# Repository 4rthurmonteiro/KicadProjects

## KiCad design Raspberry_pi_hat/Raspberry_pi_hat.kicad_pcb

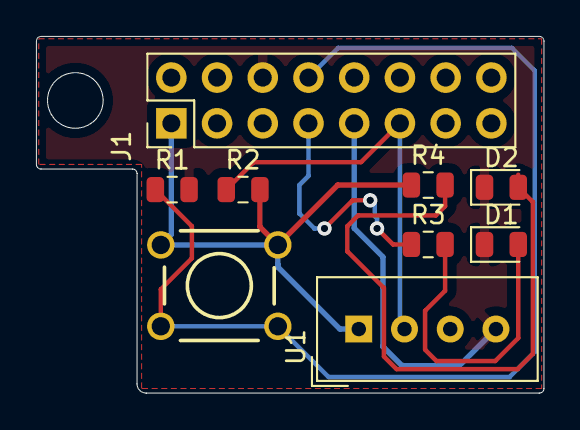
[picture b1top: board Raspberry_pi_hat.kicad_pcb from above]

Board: 2 copper layers, 28.2 x 19.8 mm, 9 parts (0 on the bottom side), 7 nets.

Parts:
D1, D2: LED; LED_0805_2012Metric
J1: Raspberry_Pi_2_3; PinHeader_2x08_P2.54mm_Vertical
R1, R2, R3, R4: R; R_0805_2012Metric
SW1: SW_DPST; SW_PUSHBUTTON_PTH
U1: DHT22; Aosong_DHT11_5.5x12.0_P2.54mm

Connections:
/3V3: J1.1, R2.2, R4.1, SW1.1, U1.1
/BUTTON_INPUT: J1.8, R1.1, SW1.2
/LED_OUTPUT: J1.7, R3.1
GND: D1.1, D2.1, J1.6, J1.9, R1.2, U1.4
unnamed: D1.2, R3.2
unnamed: D2.2, R4.2
unnamed: J1.11, R2.1, U1.2

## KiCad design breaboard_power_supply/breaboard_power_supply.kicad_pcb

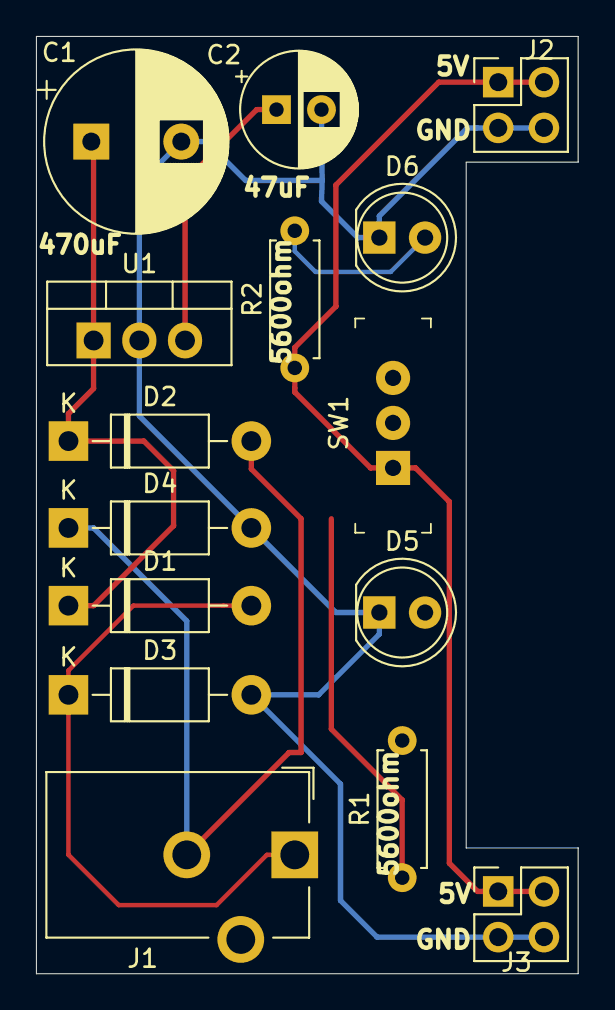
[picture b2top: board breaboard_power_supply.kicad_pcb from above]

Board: 2 copper layers, 30.1 x 52.1 mm, 15 parts (0 on the bottom side), 8 nets.

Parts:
C1: CP; CP_Radial_D10.0mm_P5.00mm
C2: CP; CP_Radial_D6.3mm_P2.50mm
D1, D2, D3, D4: 1N4007; D_DO-41_SOD81_P10.16mm_Horizontal
D5, D6: LED; LED_D5.0mm
J1: Barrel_Jack_Switch; BarrelJack_CUI_PJ-102AH_Horizontal
J2, J3: Conn_02x02_Odd_Even; PinHeader_2x02_P2.54mm_Vertical
R1, R2: R; R_Axial_DIN0207_L6.3mm_D2.5mm_P7.62mm_Horizontal
SW1: SW_DPDT_x2; Switch_Slide_11.6x4mm_EG1218
U1: LM7805_TO220; TO-220-3_Vertical

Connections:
/V-: C1.2, C2.2, D3.2, D4.2, D5.1, D6.1, J2.3, J2.4, J3.3, J3.4, U1.2
/Vin: C1.1, D1.1, D2.1, U1.1
/Vout1: C2.1, R1.1, SW1.2, U1.3
/Vout2: J2.1, J2.2, J3.1, J3.2, R2.1, SW1.1
unnamed: D1.2, D3.1, J1.1
unnamed: D2.2, D4.1, J1.2
unnamed: D5.2, R1.2
unnamed: D6.2, R2.2
